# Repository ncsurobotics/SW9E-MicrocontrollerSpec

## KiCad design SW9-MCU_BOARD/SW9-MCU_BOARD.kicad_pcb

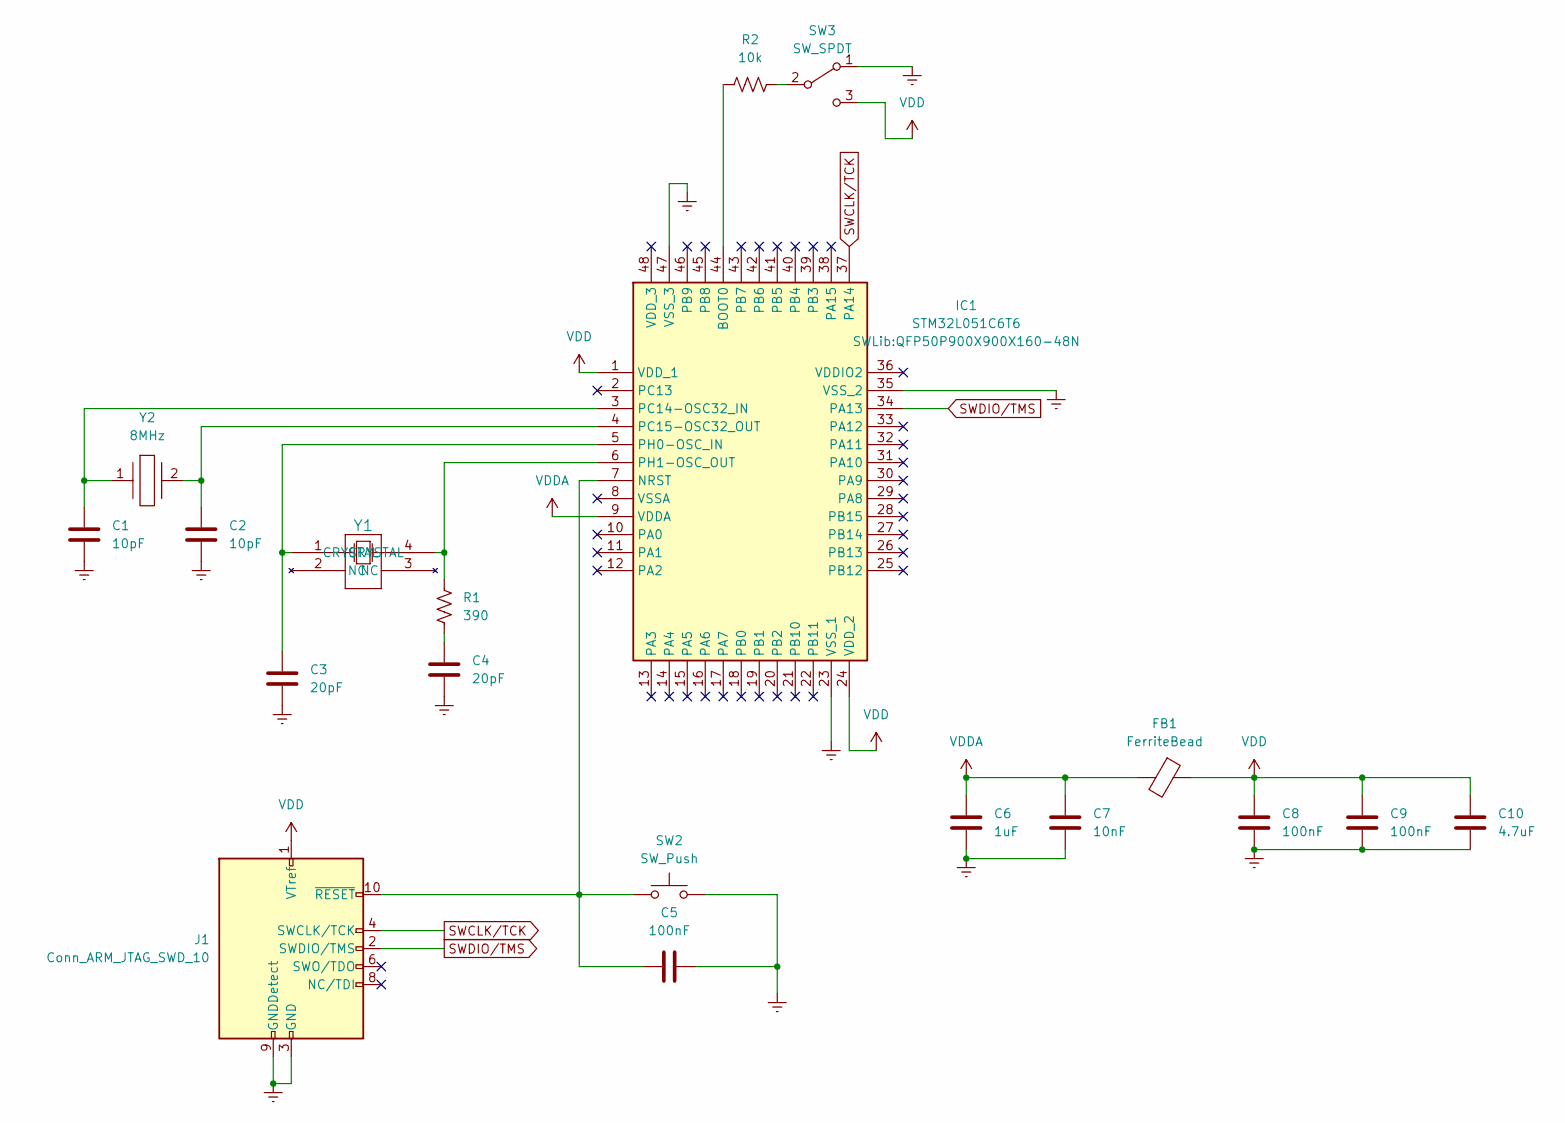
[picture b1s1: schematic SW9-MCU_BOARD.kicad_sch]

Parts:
C1, C2: 10pF; C_0603_1608Metric_Pad1.08x0.95mm_HandSolder
C3, C4: 20pF; C_0603_1608Metric_Pad1.08x0.95mm_HandSolder
C5, C8, C9: 100nF; C_0603_1608Metric_Pad1.08x0.95mm_HandSolder
C6: 1uF; C_0603_1608Metric_Pad1.08x0.95mm_HandSolder
C7: 10nF; C_0603_1608Metric_Pad1.08x0.95mm_HandSolder
C10: 4.7uF; C_0603_1608Metric_Pad1.08x0.95mm_HandSolder
FB1: FerriteBead; L_0201_0603Metric_Pad0.64x0.40mm_HandSolder
IC1: STM32L051C6T6; QFP50P900X900X160-48N; Manufacturer_Part_Number STM32L051C6T6; Mouser Part Number 511-STM32L051C6T6
J1: Conn_ARM_JTAG_SWD_10; PinSocket_1x10_P2.00mm_Vertical
R1: 390; R_0603_1608Metric_Pad0.98x0.95mm_HandSolder
R2: 10k; R_0603_1608Metric_Pad0.98x0.95mm_HandSolder
SW2: SW_Push; SW_Push_2P2T_Toggle_CK_PVA2OAH5xxxxxxV2
SW3: SW_SPDT; SW_SPDT_PCM12
Y1: ABS25-32.768KHZ-6-T; X_ABS25_ABR
Y2: 8MHz; 830003151; Mouser Part Number 710-830003151

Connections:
GND: C1.2, C2.2, C3.2, C4.2, C5.2, C6.2, C7.2, C8.2, C9.2, C10.2, IC1.23 (VSS_1), IC1.35 (VSS_2), IC1.47 (VSS_3), J1.3 (GND), J1.5 (GND), J1.9 (GNDDetect), SW2.2, SW3.1 (A)
unnamed: C4.1, R1.2
unnamed: IC1.44 (BOOT0), R2.1
unnamed: C5.1, IC1.7 (NRST), J1.10 (~RESET), SW2.1
unnamed: C1.1, IC1.3 (PC14-OSC32_IN), Y2.1
unnamed: C2.1, IC1.4 (PC15-OSC32_OUT), Y2.2
unnamed: C3.1, IC1.5 (PH0-OSC_IN), Y1.1 (CRYSTAL)
unnamed: IC1.6 (PH1-OSC_OUT), R1.1, Y1.4 (CRYSTAL)
unnamed: R2.2, SW3.2 (B)
SWCLK/TCK: IC1.37 (PA14), J1.4 (SWCLK/TCK)
SWDIO/TMS: IC1.34 (PA13), J1.2 (SWDIO/TMS)
VDD: C8.1, C9.1, C10.1, FB1.1, IC1.1 (VDD_1), IC1.24 (VDD_2), J1.1 (VTref), SW3.3 (C)
VDDA: C6.1, C7.1, FB1.2, IC1.9 (VDDA)

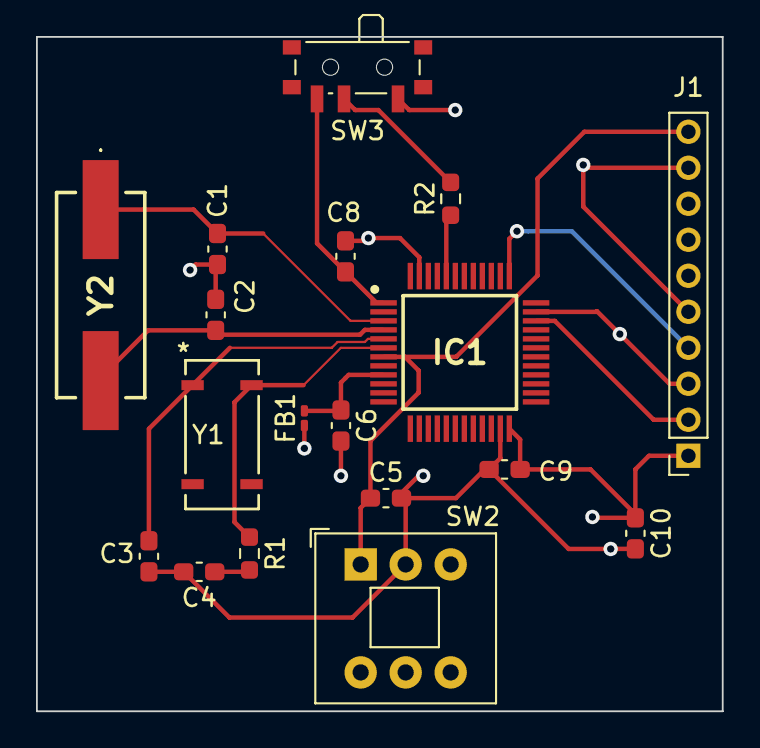
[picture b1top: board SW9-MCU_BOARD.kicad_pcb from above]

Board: 4 copper layers, 38.1 x 37.5 mm, 18 parts (0 on the bottom side), 13 nets.

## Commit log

2024-01-25 Add gitignore
2024-01-30 footprint initial design
2024-01-30 schematic cleanup
2024-01-30 more schematic cleanup
2024-01-30 schematic draft finalized
2024-02-08 Fixed minor alignment issue
2024-03-05 update stuff
2024-03-05 layout
2024-03-07 change footprints for oscillators
2024-03-25 some changes ig???
2024-03-27 more routing
2024-03-28 first layout done
2024-04-03 actually connect vdd
2024-04-08 change earth to gnd
2024-09-23 Added labels to MCU schematic
